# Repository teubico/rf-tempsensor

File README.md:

# rf-tempsensor
A simple programmable RF temperature &amp; humidity sensor with Arduino y ATTiny85

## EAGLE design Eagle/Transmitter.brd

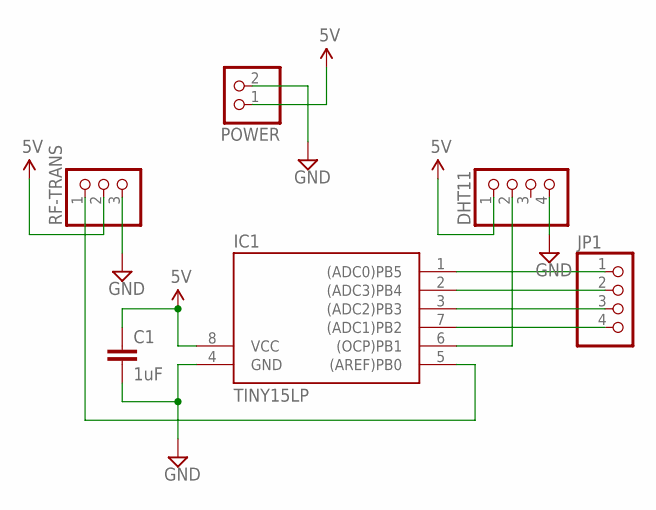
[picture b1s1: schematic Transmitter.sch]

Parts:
C1: 1uF; 0805
DHT11: PINHD-1X4; 1X04
IC1: TINY15LP; DIL08
JP1: PINHD-1X4; 1X04
POWER: PINHD-1X2; 1X02
RF-TRANS: PINHD-1X3; 1X03

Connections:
5V: C1.1, DHT11.1, IC1.8 (VCC), POWER.1, RF-TRANS.2
GND: C1.2, DHT11.4, IC1.4 (GND), POWER.2, RF-TRANS.3
unnamed: IC1.5 ((AREF)PB0), RF-TRANS.1
unnamed: DHT11.2, IC1.6 ((OCP)PB1)
unnamed: IC1.1 ((ADC0)PB5), JP1.1
unnamed: IC1.2 ((ADC3)PB4), JP1.2
unnamed: IC1.3 ((ADC2)PB3), JP1.3
unnamed: IC1.7 ((ADC1)PB2), JP1.4

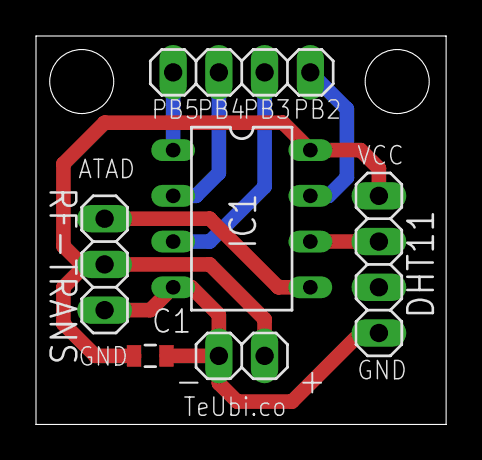
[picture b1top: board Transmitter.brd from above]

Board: 2 copper layers, 22.8 x 21.6 mm, 6 parts (0 on the bottom side), 8 nets.

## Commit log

2015-12-07 Added design files
2015-12-07 Disabled LCD by default
2015-12-07 Added README.md
    Added readme

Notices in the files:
parts and their libraries:
SparkFun-Capacitors: Licensing: Creative Commons ShareAlike 4.0 International - https://creativecommons.org/licenses/by-sa/4.0
